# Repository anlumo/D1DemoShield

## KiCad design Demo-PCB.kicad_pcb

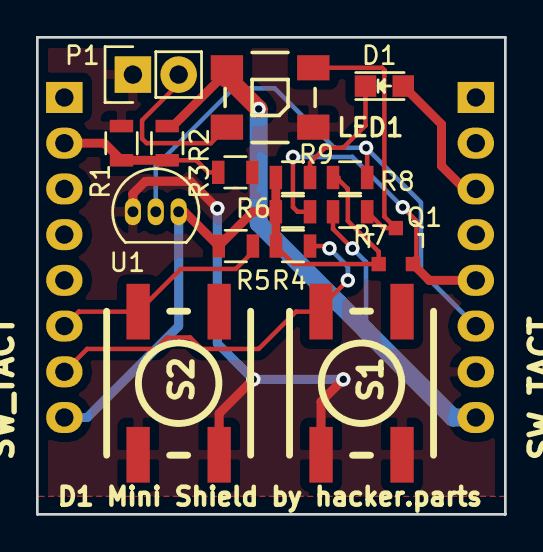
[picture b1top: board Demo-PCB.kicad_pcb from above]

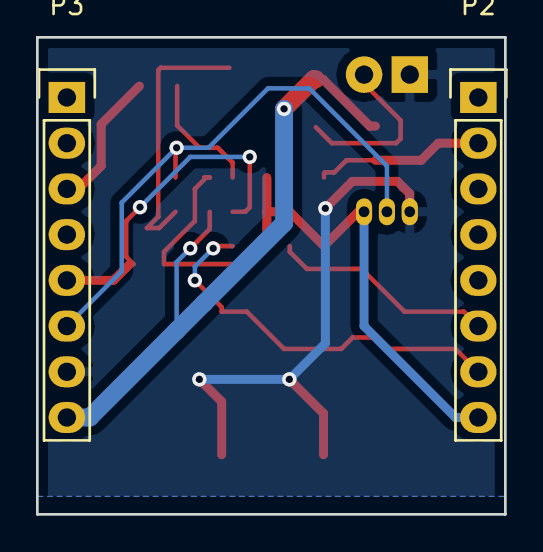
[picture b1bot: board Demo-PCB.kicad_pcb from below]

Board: 2 copper layers, 26.0 x 26.5 mm, 18 parts (2 on the bottom side), 12 nets.

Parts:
D1: LED; LED_0805
LED1: WS2812B
P1: WS2812B_OUT; Socket_Strip_Straight_1x02
P2: LEFT_ESP8266; Pin_Header_Straight_1x08
P3: RIGHT_ESP8266; Pin_Header_Straight_1x08
Q1: BSS138; SOT-23
R1: LDR; R_0805
R2, R4, R5, R6, R7: 10kΩ; R_0805
R3: 1.8kΩ; R_0805
R8: 4.7kΩ; R_0805
R9: 220Ω; R_0805
S1, S2: SW_TACT; SW_M6_SMD
U1: DS18B20; TO-92_Inline_Narrow_Oval

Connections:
+3.3V: P2.8, Q1.1, R4.1, R5.1, R6.1, R8.1, R9.1, U1.3
+5V: LED1.1, P3.8, R2.1, R7.1
GND: LED1.3, P1.1, P3.7, R1.2, R3.2, S1.1, S1.2, S2.1, S2.2, U1.1
unnamed: D1.1, R9.2
unnamed: D1.2, P3.3
unnamed: LED1.2, P1.2
unnamed: LED1.4, Q1.3, R7.2
unnamed: P2.2, R1.1, R2.2, R3.1
unnamed: P2.6, R5.2, S2.3
unnamed: P2.7, R4.2, S1.3
unnamed: P3.5, Q1.2, R6.2
unnamed: P3.6, R8.2, U1.2

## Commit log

2016-11-22 Added project files and all submodules.
